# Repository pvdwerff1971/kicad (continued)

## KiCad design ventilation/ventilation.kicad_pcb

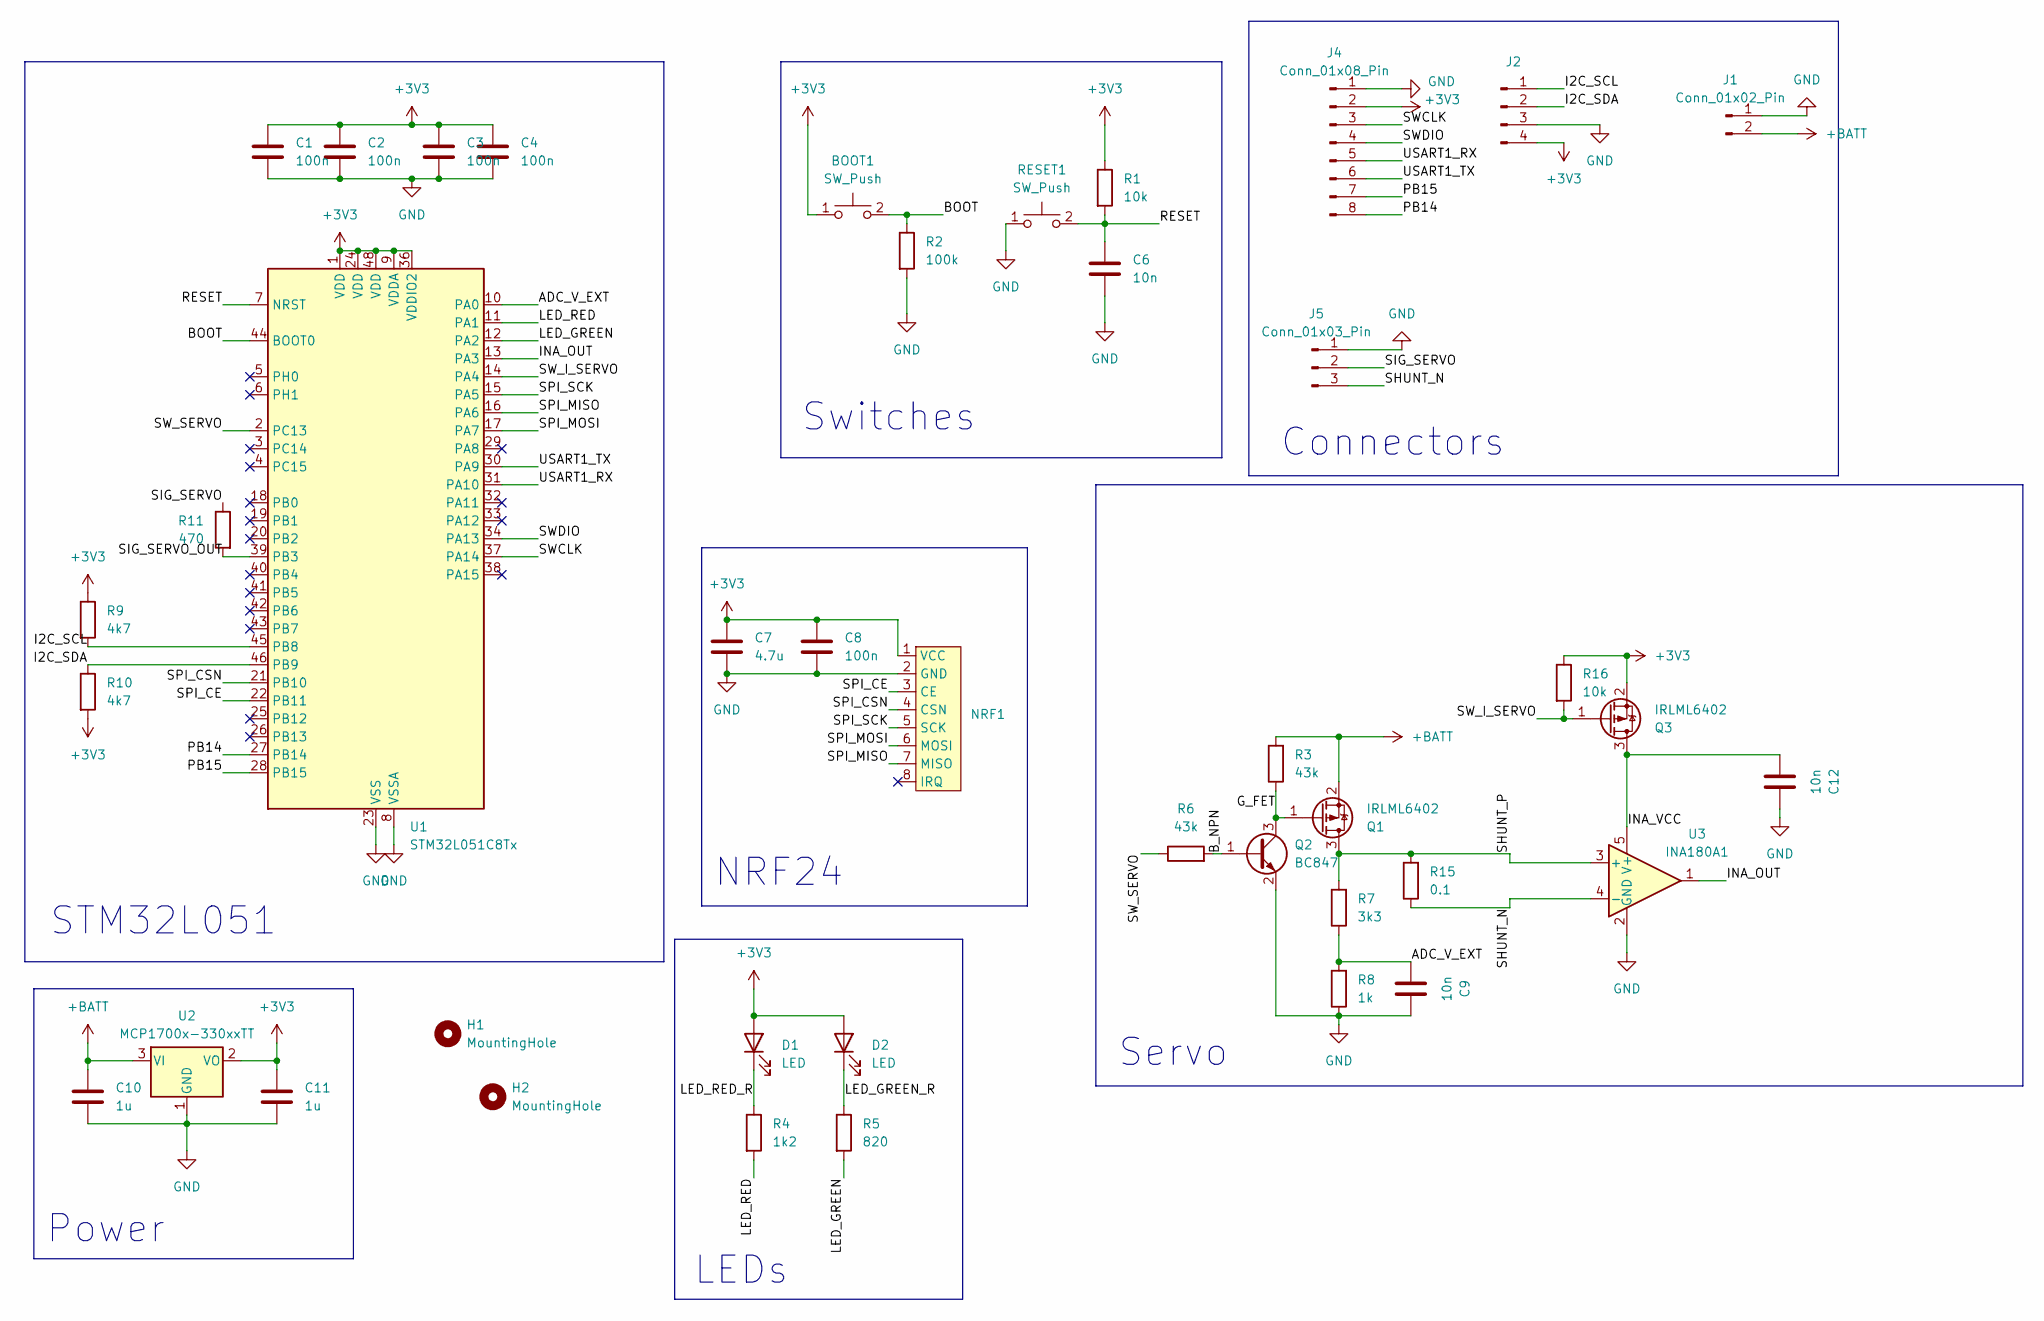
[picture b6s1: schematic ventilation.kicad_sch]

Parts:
BOOT1: SW_Push; SW_Push_4Pin
C1, C2, C3, C4, C8: 100n; C_0805_2012Metric_Pad1.18x1.45mm_HandSolder
C6, C9, C12: 10n; C_0805_2012Metric
C7: 4.7u; C_0805_2012Metric_Pad1.18x1.45mm_HandSolder
C10, C11: 1u; C_0805_2012Metric_Pad1.18x1.45mm_HandSolder
D1, D2: LED; LED_0805_2012Metric
H1, H2: MountingHole; MountingHole_2.5mm
J1: Conn_01x02_Pin; Connector_1x2_p2.54_horizontal
J2: Conn_01x04_Pin; Connector_1x4_p2.54_hortizontal
J4: Conn_01x08_Pin; PinHeader_1x08_P2.54mm_Vertical
J5: Conn_01x03_Pin; Connector_1x3_p2.54_hortizontal
NRF1: NRF24L01MINI
Q1, Q3: IRLML6402; SOT-23
Q2: BC847; SOT-23
R1: 10k; R_0805_2012Metric
R2: 100k; R_0805_2012Metric
R3: 43k; R_0805_2012Metric_Pad1.20x1.40mm_HandSolder
R4: 1k2; R_0805_2012Metric
R5: 820; R_0805_2012Metric
R6: 43k; R_0805_2012Metric
R7: 3k3; R_0805_2012Metric
R8: 1k; R_0805_2012Metric
R9, R10: 4k7; R_0805_2012Metric_Pad1.20x1.40mm_HandSolder
R11: 470; R_0805_2012Metric
R15: 0.1; R_2512_6332Metric_Pad1.40x3.35mm_HandSolder
R16: 10k; R_0805_2012Metric_Pad1.20x1.40mm_HandSolder
RESET1: SW_Push; SW_Push_4Pin
U1: STM32L051C8Tx; LQFP-48_7x7mm_P0.5mm
U2: MCP1700x-330xxTT; SOT-23_Handsoldering
U3: INA180A1; SOT-23-5

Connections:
+3V3: BOOT1.1, C1.1, C2.1, C3.1, C4.1, C7.1, C8.1, C11.1, D1.2 (A), D2.2 (A), J2.4, J4.2, NRF1.1 (VCC), Q3.2 (S), R1.1, R9.1, R10.2, R16.1, U1.1 (VDD), U1.9 (VDDA), U1.24 (VDD), U1.36 (VDDIO2), U1.48 (VDD), U2.2 (VO)
+BATT: C10.1, J1.2, Q1.2 (S), R3.2, U2.3 (VI)
/ADC_V_EXT: C9.2, R7.1, R8.2, U1.10 (PA0)
/BOOT: BOOT1.2, R2.1, U1.44 (BOOT0)
/B_NPN: Q2.1 (B), R6.2
/G_FET: Q1.1 (G), Q2.3 (C), R3.1
/I2C_SCL: J2.1, R9.2, U1.45 (PB8)
/I2C_SDA: J2.2, R10.1, U1.46 (PB9)
/INA_OUT: U1.13 (PA3), U3.1
/INA_VCC: C12.2, Q3.3 (D), U3.5 (V+)
/LED_GREEN: R5.2, U1.12 (PA2)
/LED_GREEN_R: D2.1 (K), R5.1
/LED_RED: R4.2, U1.11 (PA1)
/LED_RED_R: D1.1 (K), R4.1
/PB14: J4.8, U1.27 (PB14)
/PB15: J4.7, U1.28 (PB15)
/RESET: C6.1, R1.2, RESET1.2, U1.7 (NRST)
/SHUNT_N: J5.3, R15.1, U3.4 (-)
/SHUNT_P: Q1.3 (D), R7.2, R15.2, U3.3 (+)
/SIG_SERVO: J5.2, R11.1
/SIG_SERVO_OUT: R11.2, U1.39 (PB3)
/SPI_CE: NRF1.3 (CE), U1.22 (PB11)
/SPI_CSN: NRF1.4 (CSN), U1.21 (PB10)
/SPI_MISO: NRF1.7 (MISO), U1.16 (PA6)
/SPI_MOSI: NRF1.6 (MOSI), U1.17 (PA7)
/SPI_SCK: NRF1.5 (SCK), U1.15 (PA5)
/SWCLK: J4.3, U1.37 (PA14)
/SWDIO: J4.4, U1.34 (PA13)
/SW_I_SERVO: Q3.1 (G), R16.2, U1.14 (PA4)
/SW_SERVO: R6.1, U1.2 (PC13)
/USART1_RX: J4.5, U1.31 (PA10)
/USART1_TX: J4.6, U1.30 (PA9)
GND: C1.2, C2.2, C3.2, C4.2, C6.2, C7.2, C8.2, C9.1, C10.2, C11.2, C12.1, J1.1, J2.3, J4.1, J5.1, NRF1.2 (GND), Q2.2 (E), R2.2, R8.1, RESET1.1, U1.8 (VSSA), U1.23 (VSS), U1.35 (VSS), U1.47 (VSS), U2.1 (GND), U3.2 (GND)

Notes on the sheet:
Connectors
Servo
NRF24
Power
LEDs
Switches
STM32L051

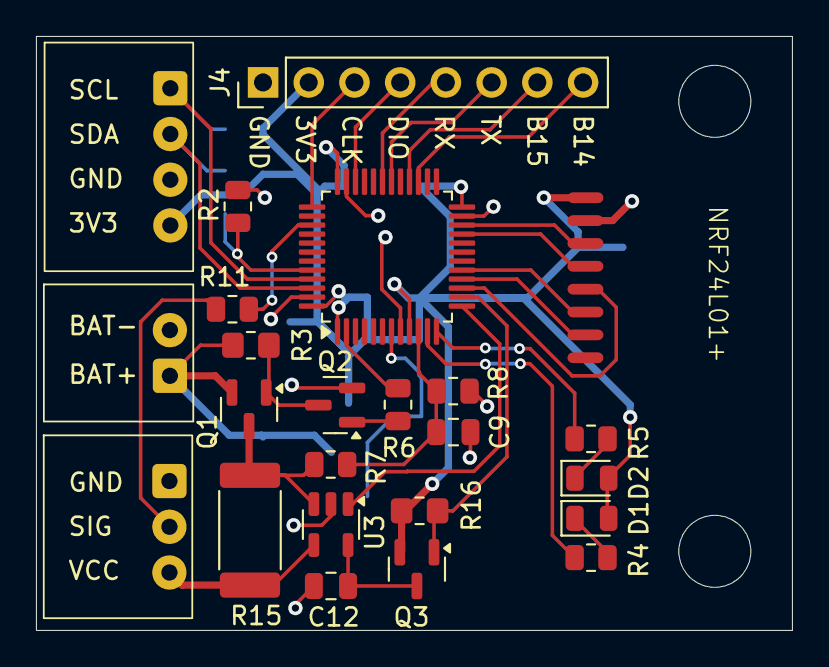
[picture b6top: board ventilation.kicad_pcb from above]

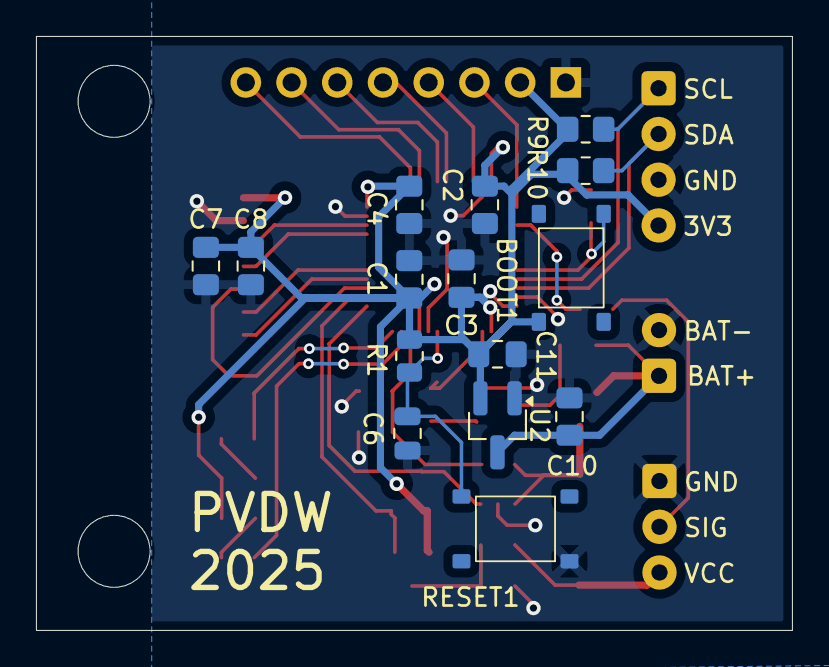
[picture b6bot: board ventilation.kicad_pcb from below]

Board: 2 copper layers, 42.0 x 33.0 mm, 41 parts (15 on the bottom side), 33 nets.

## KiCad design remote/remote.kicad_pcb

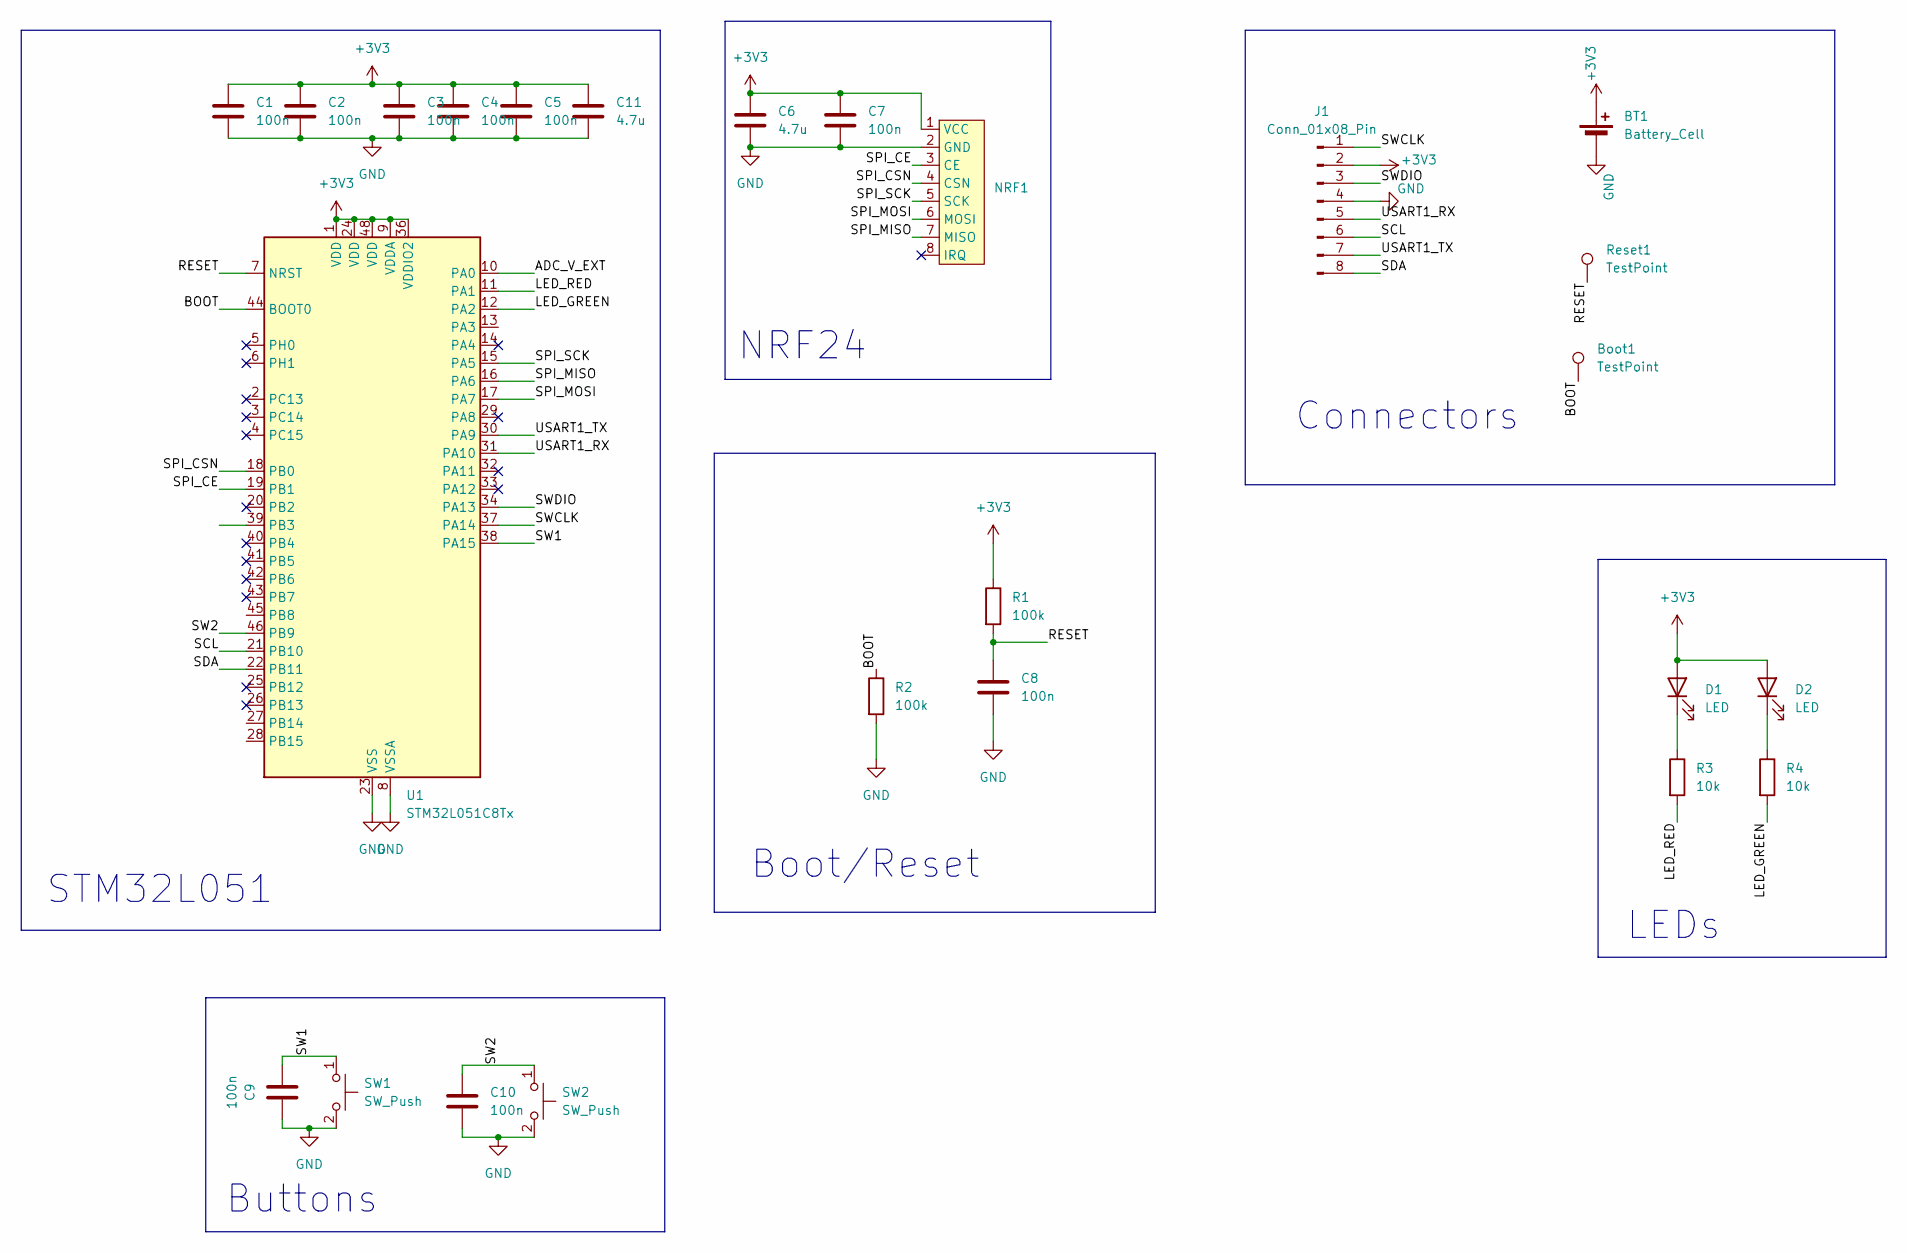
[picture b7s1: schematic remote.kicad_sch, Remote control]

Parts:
BT1: Battery_Cell; CR2032_SMD
Boot1: TestPoint; TestPoint_Pad_2.0x2.0mm
C1, C2, C3, C4, C5, C7, C8, C9, C10: 100n; C_0805_2012Metric_Pad1.18x1.45mm_HandSolder
C6, C11: 4.7u; C_0805_2012Metric_Pad1.18x1.45mm_HandSolder
D1, D2: LED; LED_0805_2012Metric
J1: Conn_01x08_Pin; PinHeader_2x04_P2.54mm_Vertical
NRF1: NRF24L01MINI
R1, R2: 100k; R_0805_2012Metric
R3, R4: 10k; R_0805_2012Metric
Reset1: TestPoint; TestPoint_Pad_2.0x2.0mm
SW1, SW2: SW_Push; SW_Push_4Pin
U1: STM32L051C8Tx; LQFP-48_7x7mm_P0.5mm

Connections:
+3V3: BT1.1 (+), C1.1, C2.1, C3.1, C4.1, C5.1, C6.1, C7.1, C11.1, D1.2 (A), D2.2 (A), J1.2, NRF1.1 (VCC), R1.1, U1.1 (VDD), U1.9 (VDDA), U1.24 (VDD), U1.36 (VDDIO2), U1.48 (VDD)
/ADC_V_EXT: U1.10 (PA0)
/BOOT: Boot1.1, R2.1, U1.44 (BOOT0)
/LED_GREEN: R4.2, U1.12 (PA2)
/LED_RED: R3.2, U1.11 (PA1)
/RESET: C8.1, R1.2, Reset1.1, U1.7 (NRST)
/SCL: J1.6, U1.21 (PB10)
/SDA: J1.8, U1.22 (PB11)
/SPI_CE: NRF1.3 (CE), U1.19 (PB1)
/SPI_CSN: NRF1.4 (CSN), U1.18 (PB0)
/SPI_MISO: NRF1.7 (MISO), U1.16 (PA6)
/SPI_MOSI: NRF1.6 (MOSI), U1.17 (PA7)
/SPI_SCK: NRF1.5 (SCK), U1.15 (PA5)
/SW1: C9.2, SW1.1, U1.38 (PA15)
/SW2: C10.1, SW2.1, U1.46 (PB9)
/SWCLK: J1.1, U1.37 (PA14)
/SWDIO: J1.3, U1.34 (PA13)
/USART1_RX: J1.5, U1.31 (PA10)
/USART1_TX: J1.7, U1.30 (PA9)
GND: BT1.2 (-), C1.2, C2.2, C3.2, C4.2, C5.2, C6.2, C7.2, C8.2, C9.1, C10.2, C11.2, J1.4, NRF1.2 (GND), R2.2, SW1.2, SW2.2, U1.8 (VSSA), U1.23 (VSS), U1.35 (VSS), U1.47 (VSS)
unnamed: D1.1 (K), R3.1
unnamed: D2.1 (K), R4.1

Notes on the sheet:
Boot/Reset
Buttons
NRF24
STM32L051
LEDs
Connectors

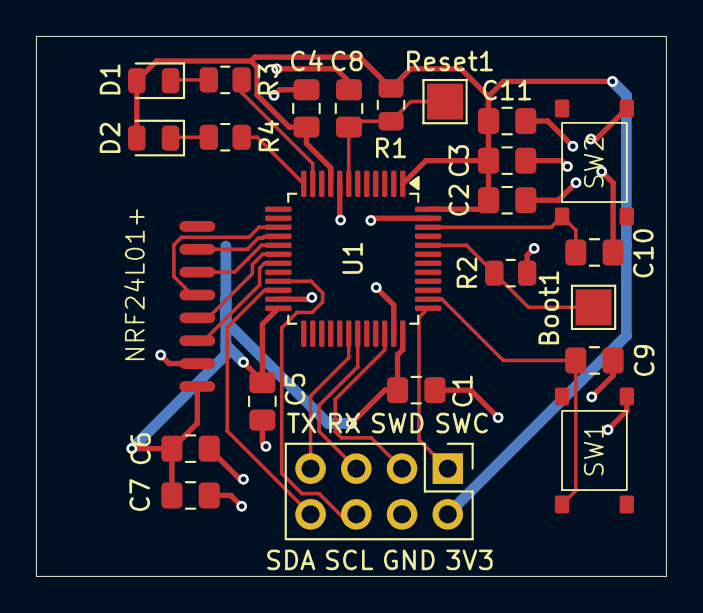
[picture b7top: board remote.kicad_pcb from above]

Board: 2 copper layers, 35.0 x 30.0 mm, 25 parts (1 on the bottom side), 21 nets.

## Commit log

2025-07-11 Initial version
2025-07-18 New version
2025-07-18 Changed SOT23 footprints to hand solder
2025-08-06 New versions
2025-08-08 Order versions
2025-08-29 New order
2026-01-15 New main controller and sensor
2026-02-24 Added PCB for robot
2026-02-24 Added PCB for robot remote control
2026-02-24 Updated robot and created 0402 test pcb
2026-03-15 New versions for Robot PCBs
2026-03-15 Fixed VCC-GND mixup on drv8833
2026-03-29 Minor bugfixes in Robot PCB (UART connected to the wrong pin of the stepper driver)
2026-05-28 New PCB Layout for Robot
2026-06-03 Ordered version
